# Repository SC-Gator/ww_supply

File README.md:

# Wall wart ±12V power supply and bus board

This is a power supply based on the [MFOS wall wart supply](http://musicfromouterspace.com/analogsynth_new/WALLWARTSUPPLY/WALLWARTSUPPLY.php). Differences are:

* Added polyfuses
* Added LEDs
* Input is either barrel jack or pluggable terminal block, with another pluggable terminal block for daisy chaining
* Output is a (non pluggable) terminal block
* Regulators are vertical, with space for Tayda A-5093 heat sinks
* Board is shorter and wider (100 x 61 mm) to keep fabbing price low

Note that unlike usual Eurorack supplies, this one provides no +5 V rail. (Of course there are almost no Eurorack modules that use the +5 V rail these days, and no Kosmo modules do.)

I've built a version of this board and it works. I found a few minor issues in the process, the worst of which was an incorrect footprint for the fuses with too small holes for the leads — no other problems affecting functionality. I've since updated the layout to fix the issues I've found. I haven't built that version yet, but it should be fine.

# Sonosus' Bus Board Version
I've designed a snap off bus board into the PCB. The board size is just large enough to be eligible for a free coupon at [a certain PCB fab house](https://allpcb.com) (no, I am not affiliated with them in any way, this board will probably work with JLCPCB, OSHPark, PCBWay, Eurocircuits, etc, etc, etc.) 

You can use it as a power supply with integrated bus board, or snap them apart and wire seperately.

Interactive BOM is [here](http://htmlpreview.github.io/?https://github.com/Sonosus/ww_supply/blob/main/Docs/mfosish_ww_supply.html).

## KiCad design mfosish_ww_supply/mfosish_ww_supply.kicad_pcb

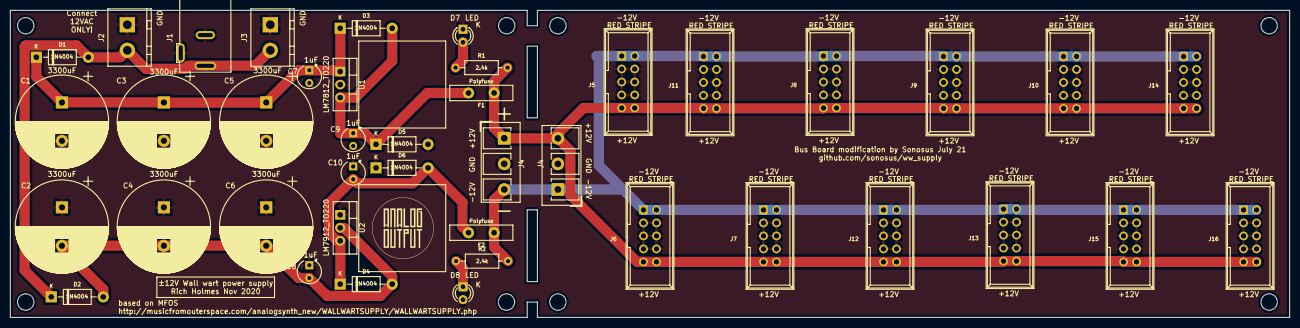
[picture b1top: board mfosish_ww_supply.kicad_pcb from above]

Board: 2 copper layers, 250.0 x 60.0 mm, 52 parts (0 on the bottom side), 10 nets.

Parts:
C1, C2, C3, C4, C5, C6: 3300uF; CP_Radial_D18.0mm_P7.50mm
C7, C8, C9, C10: 1uF; CP_Radial_Tantal_D4.5mm_P2.50mm
D1, D2, D3, D4, D5, D6: 1N4004; D_DO-41_SOD81_P10.16mm_Horizontal
D7, D8: LED; LED_D3.0mm
F1, F2: Polyfuse; PPTC_RXEF110
GRAF1: AO logo; analogoutput_12mm
H1, H2, H3, H4, H4#2, H4#3, H4#4, H4#5: MountingHole; MountingHole_3.2mm_M3
HS1, HS2: Heatsink; Heatsink_17x17mm_A-5093
J1: Conn_01x03; Wall_wart_A-4118
J2, J3: Conn_01x02; TerminalBlock_dinkle_pluggable_2_P5.00mm
J4, J4#2: Conn_01x03; TerminalBlock_Degson_DG301_1x03_P5.00mm_Vertical
J5, J6, J7, J8, J9, J10, J11, J12, J13, J14, J15, J16: Synth_power_2x5; Power_Header
R1, R2: 2.4k; R_Axial_DIN0207_L6.3mm_D2.5mm_P10.16mm_Horizontal
U1: LM7812_TO220; TO-220-3_Vertical
U2: LM7912_TO220; TO-220-3_Vertical

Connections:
+12V: F1.1, J4.3, J4#2.1, J5.9, J5.10, J6.9, J6.10, J7.9, J7.10, J8.9, J8.10, J9.9, J9.10, J10.9, J10.10, J11.9, J11.10, J12.9, J12.10, J13.9, J13.10, J14.9, J14.10, J15.9, J15.10, J16.9, J16.10, R1.2
-12V: F2.1, J4.1, J4#2.3, J5.1, J5.2, J6.1, J6.2, J7.1, J7.2, J8.1, J8.2, J9.1, J9.2, J10.1, J10.2, J11.1, J11.2, J12.1, J12.2, J13.1, J13.2, J14.1, J14.2, J15.1, J15.2, J16.1, J16.2, R2.2
GND: C1.2, C2.1, C3.2, C4.1, C5.2, C6.1, C7.2, C8.1, C9.2, C10.1, D5.2, D6.1, D7.1, D8.2, J1.1, J1.2, J2.1, J3.1, J4.2, J4#2.2, J5.3, J5.4, J5.5, J5.6, J5.7, J5.8, J6.3, J6.4, J6.5, J6.6, J6.7, J6.8, J7.3, J7.4, J7.5, J7.6, J7.7, J7.8, J8.3, J8.4, J8.5, J8.6, J8.7, J8.8, J9.3, J9.4, J9.5, J9.6, J9.7, J9.8, J10.3, J10.4, J10.5, J10.6, J10.7, J10.8, J11.3, J11.4, J11.5, J11.6, J11.7, J11.8, J12.3, J12.4, J12.5, J12.6, J12.7, J12.8, J13.3, J13.4, J13.5, J13.6, J13.7, J13.8, J14.3, J14.4, J14.5, J14.6, J14.7, J14.8, J15.3, J15.4, J15.5, J15.6, J15.7, J15.8, J16.3, J16.4, J16.5, J16.6, J16.7, J16.8, U1.2, U2.1
unnamed: C1.1, C3.1, C5.1, C7.1, D1.1, D3.1, U1.1
unnamed: C2.2, C4.2, C6.2, C8.2, D2.2, D4.2, U2.2
unnamed: C9.1, D3.2, D5.1, F1.2, U1.3
unnamed: C10.2, D4.1, D6.2, F2.2, U2.3
unnamed: D1.2, D2.1, J1.3, J2.2, J3.2
unnamed: D7.2, R1.1
unnamed: D8.1, R2.1

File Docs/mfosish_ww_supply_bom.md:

# mfosish_ww_supply.sch BOM

Wed 18 Nov 2020 07:30:47 PM EST

Generated from schematic by Eeschema 5.1.8-db9833491~87~ubuntu20.04.1

**Component Count:** 27

| Value | Qty | Part | Description | Vendor |
| ----- | --- | ---- | ----------- | ------ |
| C1, C2, C3, C4, C5, C6 | 6 | 3300uF | Electrolytic capacitor | Tayda A-2421 |
| C7, C8, C9, C10 | 4 | 1uF | Tantalum capacitor | Tayda A-265 |
| D1, D2, D3, D4, D5, D6 | 6 | 1N4004 | 400V 1A General Purpose Rectifier Diode, DO-41 | Tayda A-156 |
| D7, D8 | 2 | LED | Light emitting diode | Tayda A-261 |
| F1, F2 | 2 | Polyfuse | Resettable fuse, polymeric positive temperature coefficient, 1.1 A (?) | Tayda A-5233 |
| J1, J3 | 2* | Conn_01x02 | Pluggable terminal block socket 2 pin | Tayda A-2481 |
| | 2* | | Pluggable terminal block 2 pin | Tayda A-672 |
| J2 | 1 | Conn_01x03 | Terminal block 3 pin | Tayda A-669 |
| R1, R2 | 2 | 2.4k | Resistor | Tayda |
| U1 | 1 | LM7812_TO220 | Positive 1A 35V Linear Regulator, Fixed Output 12V, TO-220 | Tayda A-207 |
| U2 | 1 | LM7912_TO220 | Negative 1A 35V Linear Regulator, Fixed Output 12V, TO-220 | Tayda A-505 |
| | 2 | | Heat sink | Tayda A-5093 |
    
\* Second plug and socket for daisy chaining, not required for single unit

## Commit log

2020-11-20 Few tweaks, added barrel jack
2020-11-20 More tweaks, revised jack footprint
2020-11-21 PCB revisions
2020-12-28 Fix (I hope) misconnected barrel jack
2020-12-28 Ground barrel jack switch
2021-01-17 Include lib table files; new Gerbers
2021-02-19 Footprint update
2021-02-28 Update .gitignore, DIN5
2021-05-07 Correct polyswitch footprint
2021-05-07 Rotate pluggable blocks, some new footprints; holes, logo, heatsinks on schematic
2021-05-08 No, I liked the first orientation better
2021-05-08 Updated README for V1.0
2021-05-08 New Gerbers
2021-07-14 pwr in schem
2021-07-14 extend board outline to allpcb free limits
2021-07-14 insert fps
2021-07-14 done!
2021-07-14 gerbers
2021-07-14 deprecated bom marked as such
2021-07-14 zzzzzip!
2021-07-14 ibom
2021-07-14 save
2021-08-08 csv bom
